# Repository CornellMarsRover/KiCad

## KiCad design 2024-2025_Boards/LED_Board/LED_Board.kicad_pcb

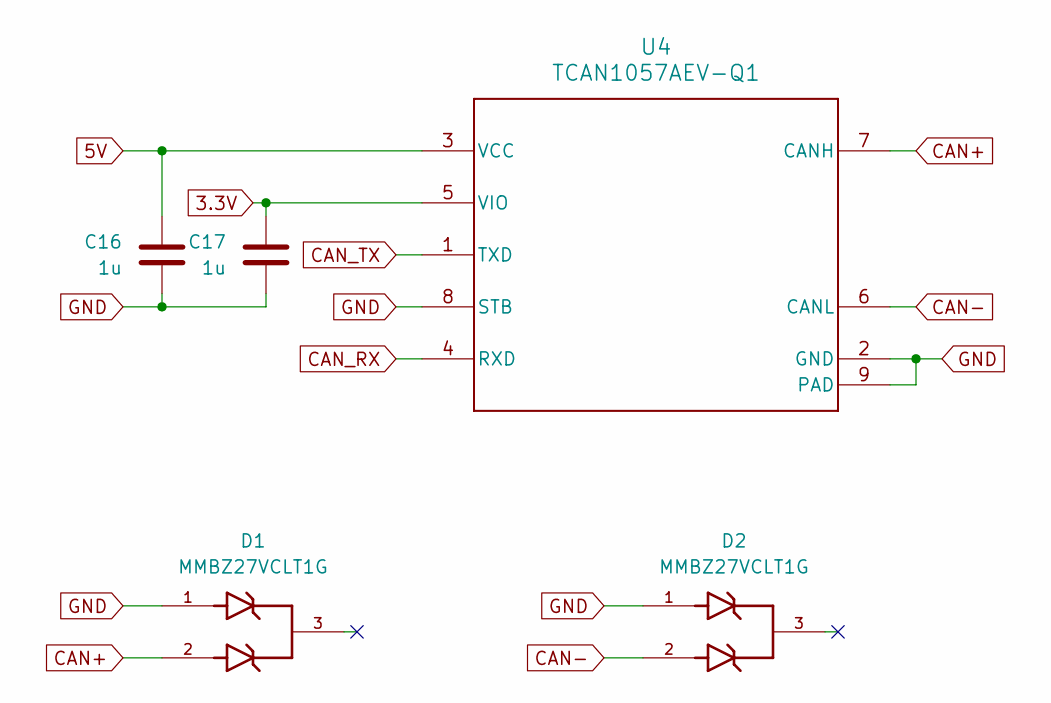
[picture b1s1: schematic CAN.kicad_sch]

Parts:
C16, C17: 1u; C_0402_1005Metric
D1, D2: MMBZ27VCLT1G; SOT95P237X111-3N; PARTREV 17
U4: TCAN1057AEV-Q1; SOIC-8_3.9x4.9mm_P1.27mm; MPN TCAN1057AEVDRQ1

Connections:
3.3V: C17.1, U4.5 (VIO); also elsewhere on the board
5V: C16.1, U4.3 (VCC); also elsewhere on the board
CAN+: D1.2, U4.7 (CANH); also elsewhere on the board
CAN-: D2.2, U4.6 (CANL); also elsewhere on the board
CAN_RX: U4.4 (RXD); also elsewhere on the board
CAN_TX: U4.1 (TXD); also elsewhere on the board
GND: C16.2, C17.2, D1.1, D2.1, U4.2 (GND), U4.8 (STB), U4.9 (PAD); also elsewhere on the board

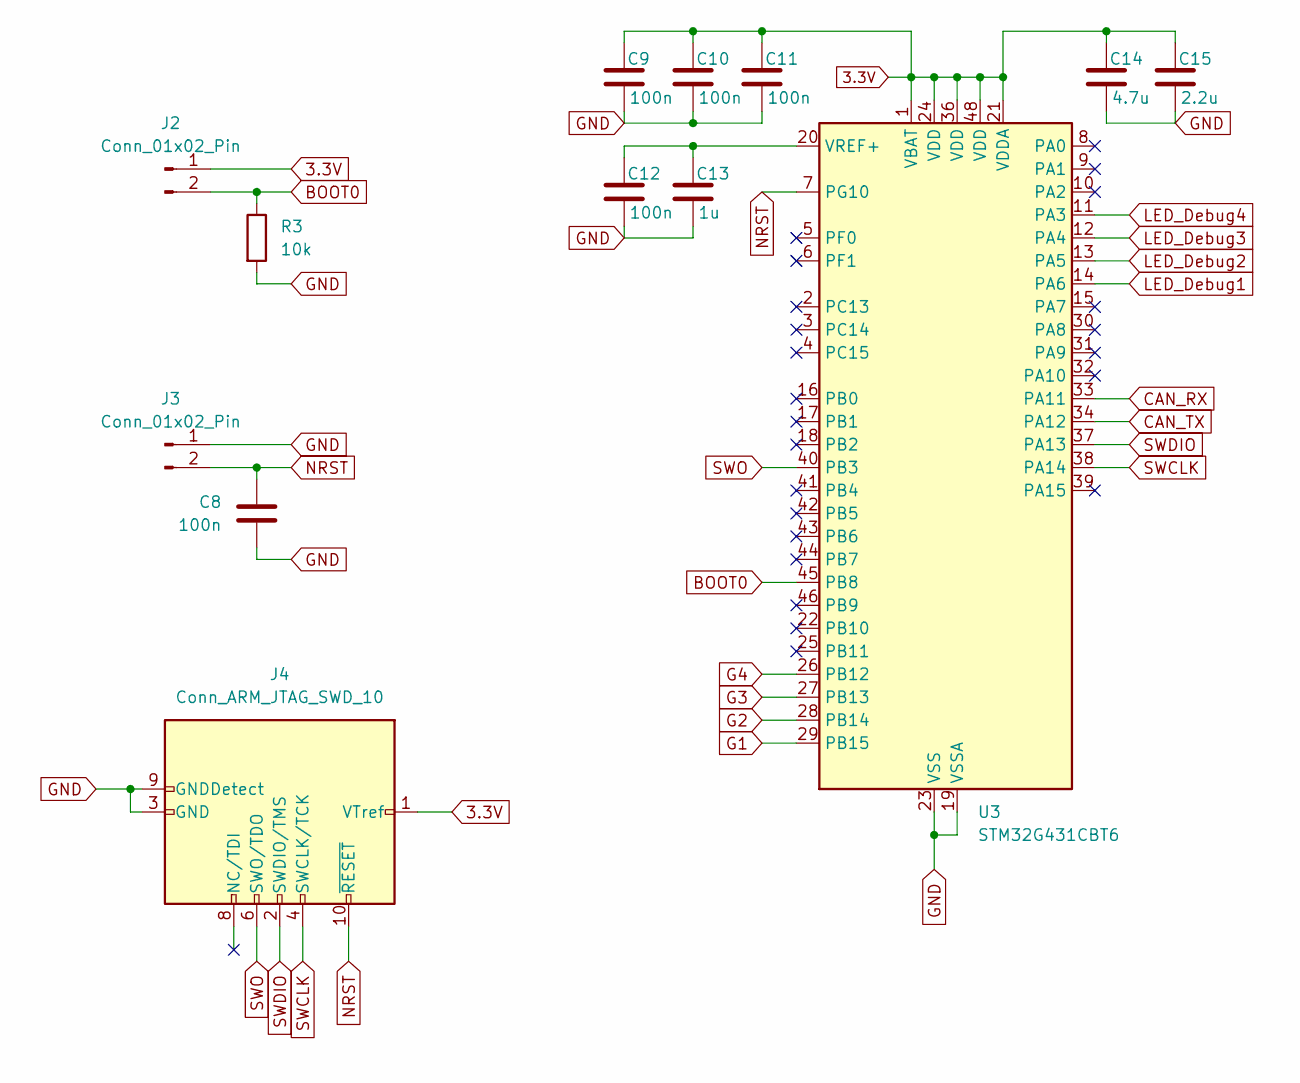
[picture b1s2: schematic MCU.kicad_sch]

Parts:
C8, C9, C10, C11, C12: 100n; C_0402_1005Metric
C13: 1u; C_0402_1005Metric
C14: 4.7u; C_0603_1608Metric
C15: 2.2u; C_0603_1608Metric
J2, J3: Conn_01x02_Pin; PinHeader_1x02_P2.54mm_Horizontal
J4: Conn_ARM_JTAG_SWD_10; PinHeader_2x05_P1.27mm_Vertical
R3: 10k; R_0402_1005Metric
U3: STM32G431CBT6; LQFP-48_7x7mm_P0.5mm

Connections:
3.3V: C9.1, C10.1, C11.1, C14.1, C15.1, J2.1, J4.1 (VTref), U3.1 (VBAT), U3.21 (VDDA), U3.24 (VDD), U3.36 (VDD), U3.48 (VDD); also elsewhere on the board
BOOT0: J2.2, R3.1, U3.45 (PB8)
CAN_RX: U3.33 (PA11); also elsewhere on the board
CAN_TX: U3.34 (PA12); also elsewhere on the board
G1: U3.29 (PB15); also elsewhere on the board
G2: U3.28 (PB14); also elsewhere on the board
G3: U3.27 (PB13); also elsewhere on the board
G4: U3.26 (PB12); also elsewhere on the board
GND: C8.2, C9.2, C10.2, C11.2, C12.2, C13.2, C14.2, C15.2, J3.1, J4.3 (GND), J4.5 (GND), J4.9 (GNDDetect), R3.2, U3.19 (VSSA), U3.23 (VSS), U3.35 (VSS), U3.47 (VSS); also elsewhere on the board
LED_Debug1: U3.14 (PA6); also elsewhere on the board
LED_Debug2: U3.13 (PA5); also elsewhere on the board
LED_Debug3: U3.12 (PA4); also elsewhere on the board
LED_Debug4: U3.11 (PA3); also elsewhere on the board
NRST: C8.1, J3.2, J4.10 (~RESET), U3.7 (PG10); also elsewhere on the board
unnamed: C12.1, C13.1, U3.20 (VREF+)
SWCLK: J4.4 (SWCLK/TCK), U3.38 (PA14)
SWDIO: J4.2 (SWDIO/TMS), U3.37 (PA13)
SWO: J4.6 (SWO/TDO), U3.40 (PB3)

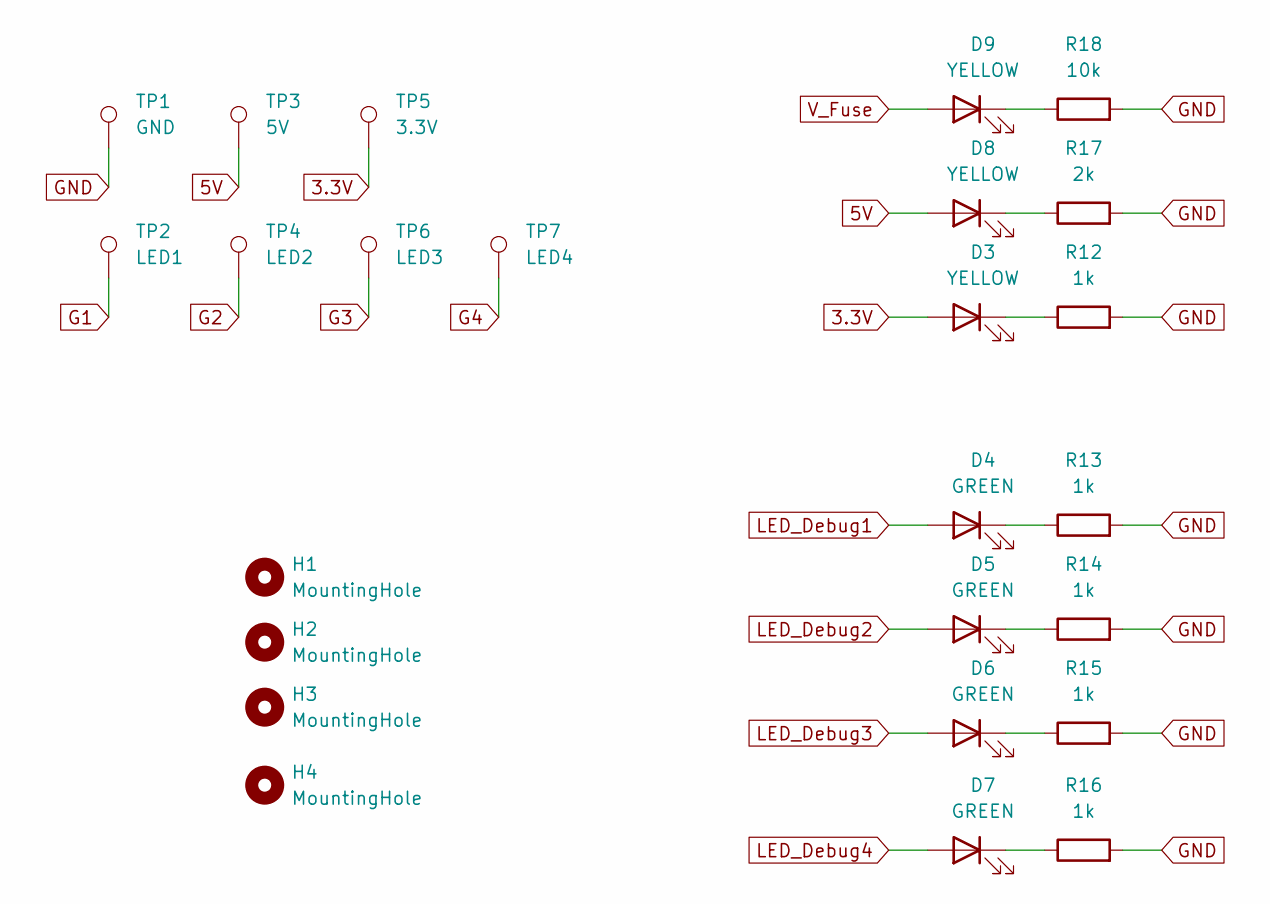
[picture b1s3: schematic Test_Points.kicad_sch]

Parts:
D3, D8, D9: YELLOW; LED_0603_1608Metric
D4, D5, D6, D7: GREEN; LED_0603_1608Metric
H1, H2, H3, H4: MountingHole; MountingHole_2.7mm_M2.5
R12, R13, R14, R15, R16: 1k; R_0402_1005Metric
R17: 2k; R_0402_1005Metric
R18: 10k; R_0402_1005Metric
TP1: GND; TestPoint_Pad_D1.0mm
TP2: LED1; TestPoint_Pad_D1.0mm
TP3: 5V; TestPoint_Pad_D1.0mm
TP4: LED2; TestPoint_Pad_D1.0mm
TP5: 3.3V; TestPoint_Pad_D1.0mm
TP6: LED3; TestPoint_Pad_D1.0mm
TP7: LED4; TestPoint_Pad_D1.0mm

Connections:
3.3V: D3.2 (A), TP5.1; also elsewhere on the board
5V: D8.2 (A), TP3.1; also elsewhere on the board
G1: TP2.1; also elsewhere on the board
G2: TP4.1; also elsewhere on the board
G3: TP6.1; also elsewhere on the board
G4: TP7.1; also elsewhere on the board
GND: R12.2, R13.2, R14.2, R15.2, R16.2, R17.2, R18.2, TP1.1; also elsewhere on the board
LED_Debug1: D4.2 (A); also elsewhere on the board
LED_Debug2: D5.2 (A); also elsewhere on the board
LED_Debug3: D6.2 (A); also elsewhere on the board
LED_Debug4: D7.2 (A); also elsewhere on the board
unnamed: D3.1 (K), R12.1
unnamed: D4.1 (K), R13.1
unnamed: D5.1 (K), R14.1
unnamed: D6.1 (K), R15.1
unnamed: D7.1 (K), R16.1
unnamed: D8.1 (K), R17.1
unnamed: D9.1 (K), R18.1
V_Fuse: D9.2 (A); also elsewhere on the board

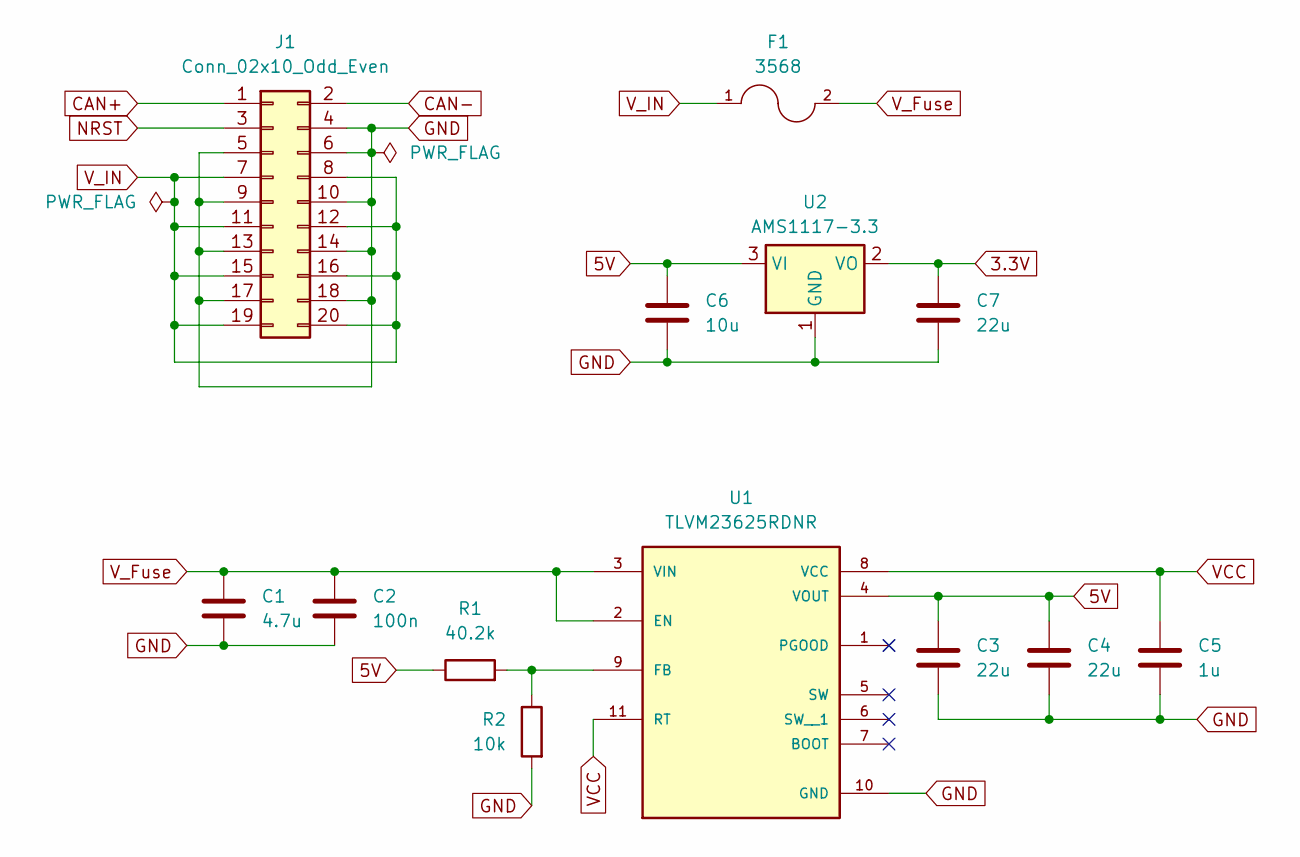
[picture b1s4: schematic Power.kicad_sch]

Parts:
C1: 4.7u; C_0805_2012Metric
C2: 100n; C_0402_1005Metric
C3, C4, C7: 22u; C_0805_2012Metric
C5: 1u; C_0402_1005Metric
C6: 10u; C_0805_2012Metric
F1: 3568; FUSE_3568; PARTREV C
J1: Conn_02x10_Odd_Even; CONN20_D10-RA-BK_SUL
R1: 40.2k; R_0603_1608Metric
R2: 10k; R_0603_1608Metric
U1: TLVM23625RDNR; RDN0011A-MFG; PARTREV B
U2: AMS1117-3.3; SOT-223-3_TabPin2

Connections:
3.3V: C7.1, U2.2 (VO); also elsewhere on the board
5V: C3.1, C4.1, C6.1, R1.1, U1.4 (VOUT), U2.3 (VI); also elsewhere on the board
CAN+: J1.1; also elsewhere on the board
CAN-: J1.2; also elsewhere on the board
GND: C1.2, C2.2, C3.2, C4.2, C5.2, C6.2, C7.2, J1.4, J1.5, J1.6, J1.9, J1.10, J1.13, J1.14, J1.17, J1.18, R2.2, U1.10 (GND), U2.1 (GND); also elsewhere on the board
NRST: J1.3; also elsewhere on the board
unnamed: R1.2, R2.1, U1.9 (FB)
VCC: C5.1, U1.8 (VCC), U1.11 (RT)
V_Fuse: C1.1, C2.1, F1.2, F1.4, U1.2 (EN), U1.3 (VIN); also elsewhere on the board
V_IN: F1.1, F1.3, J1.7, J1.8, J1.11, J1.12, J1.15, J1.16, J1.19, J1.20

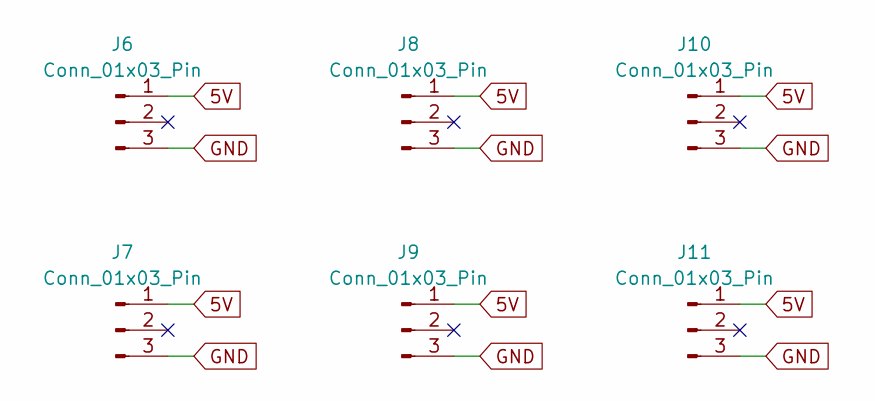
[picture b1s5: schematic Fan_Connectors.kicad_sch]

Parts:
J6, J7, J8, J9, J10, J11: Conn_01x03_Pin; CONN_A-7395-03B_MOL

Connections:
5V: J6.1, J7.1, J8.1, J9.1, J10.1, J11.1; also elsewhere on the board
GND: J6.3, J7.3, J8.3, J9.3, J10.3, J11.3; also elsewhere on the board

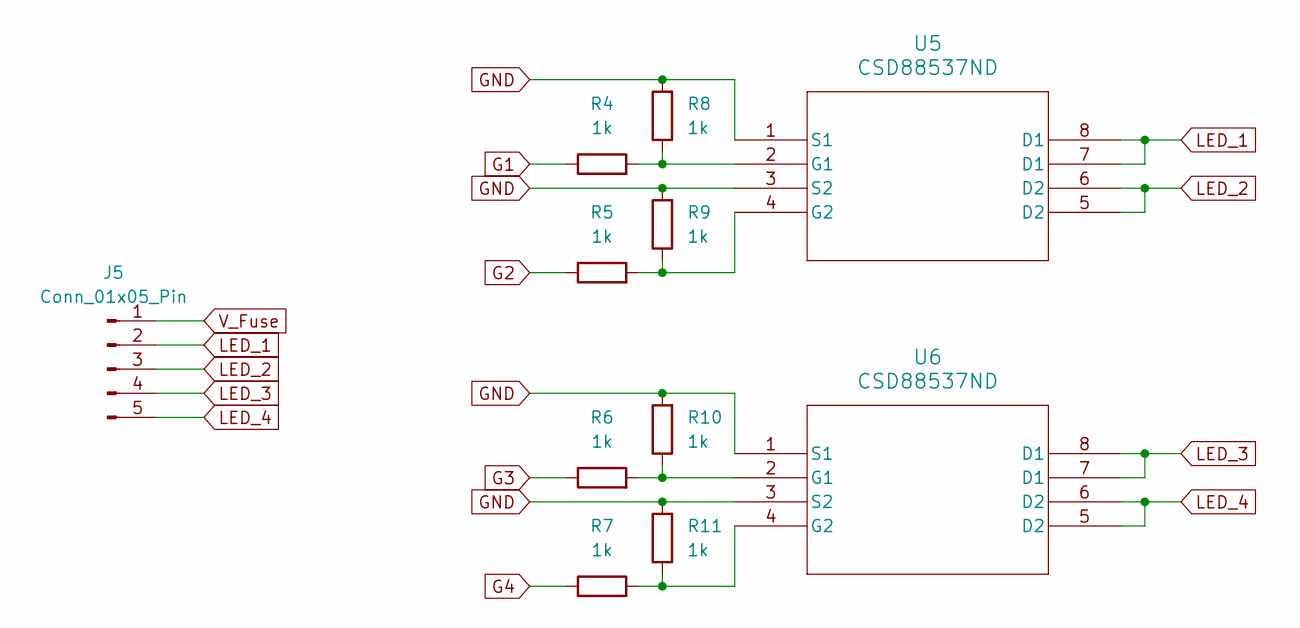
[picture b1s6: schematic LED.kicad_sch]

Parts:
J5: Conn_01x05_Pin; JST_EH_S5B-EH_1x05_P2.50mm_Horizontal
R4, R5, R6, R7, R8, R9, R10, R11: 1k; R_0402_1005Metric
U5, U6: CSD88537ND; CSD88537ND8-M

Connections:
G1: R4.1; also elsewhere on the board
G2: R5.1; also elsewhere on the board
G3: R6.1; also elsewhere on the board
G4: R7.1; also elsewhere on the board
GND: R8.2, R9.2, R10.2, R11.2, U5.1 (S1), U5.3 (S2), U6.1 (S1), U6.3 (S2); also elsewhere on the board
LED_1: J5.2, U5.7 (D1), U5.8 (D1)
LED_2: J5.3, U5.5 (D2), U5.6 (D2)
LED_3: J5.4, U6.7 (D1), U6.8 (D1)
LED_4: J5.5, U6.5 (D2), U6.6 (D2)
unnamed: R4.2, R8.1, U5.2 (G1)
unnamed: R5.2, R9.1, U5.4 (G2)
unnamed: R6.2, R10.1, U6.2 (G1)
unnamed: R7.2, R11.1, U6.4 (G2)
V_Fuse: J5.1; also elsewhere on the board

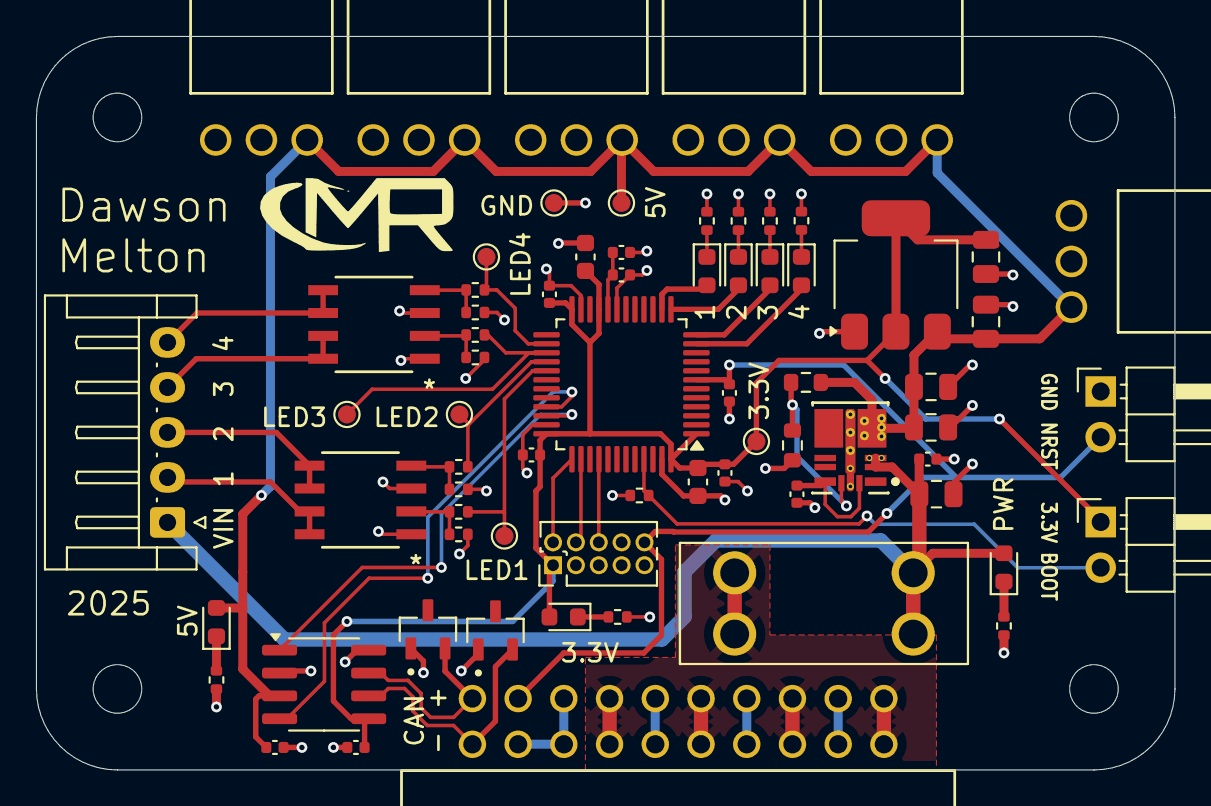
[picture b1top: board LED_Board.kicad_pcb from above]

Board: 2 copper layers, 63.2 x 40.7 mm, 73 parts (0 on the bottom side), 40 nets.

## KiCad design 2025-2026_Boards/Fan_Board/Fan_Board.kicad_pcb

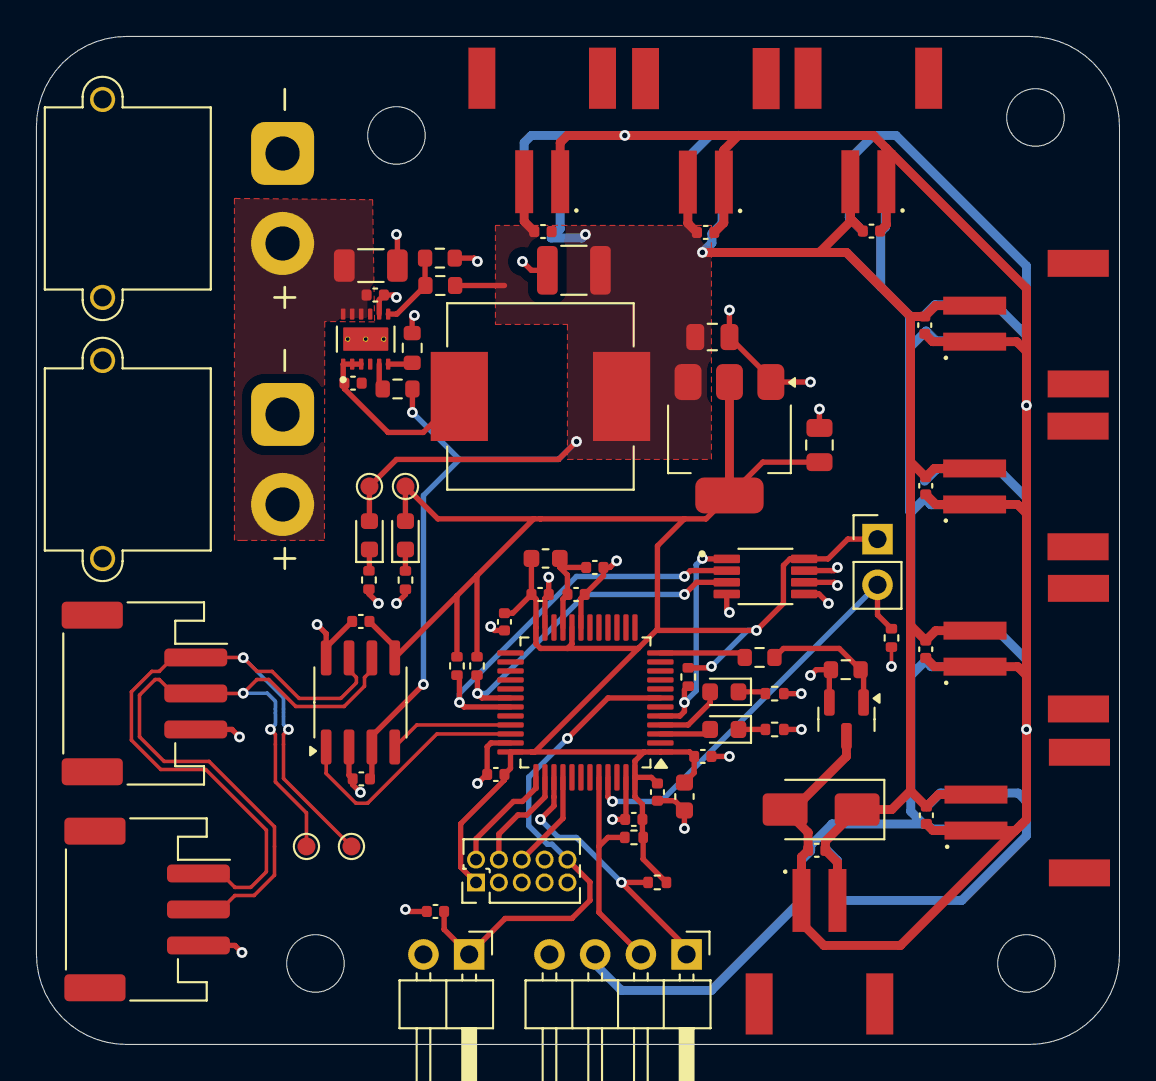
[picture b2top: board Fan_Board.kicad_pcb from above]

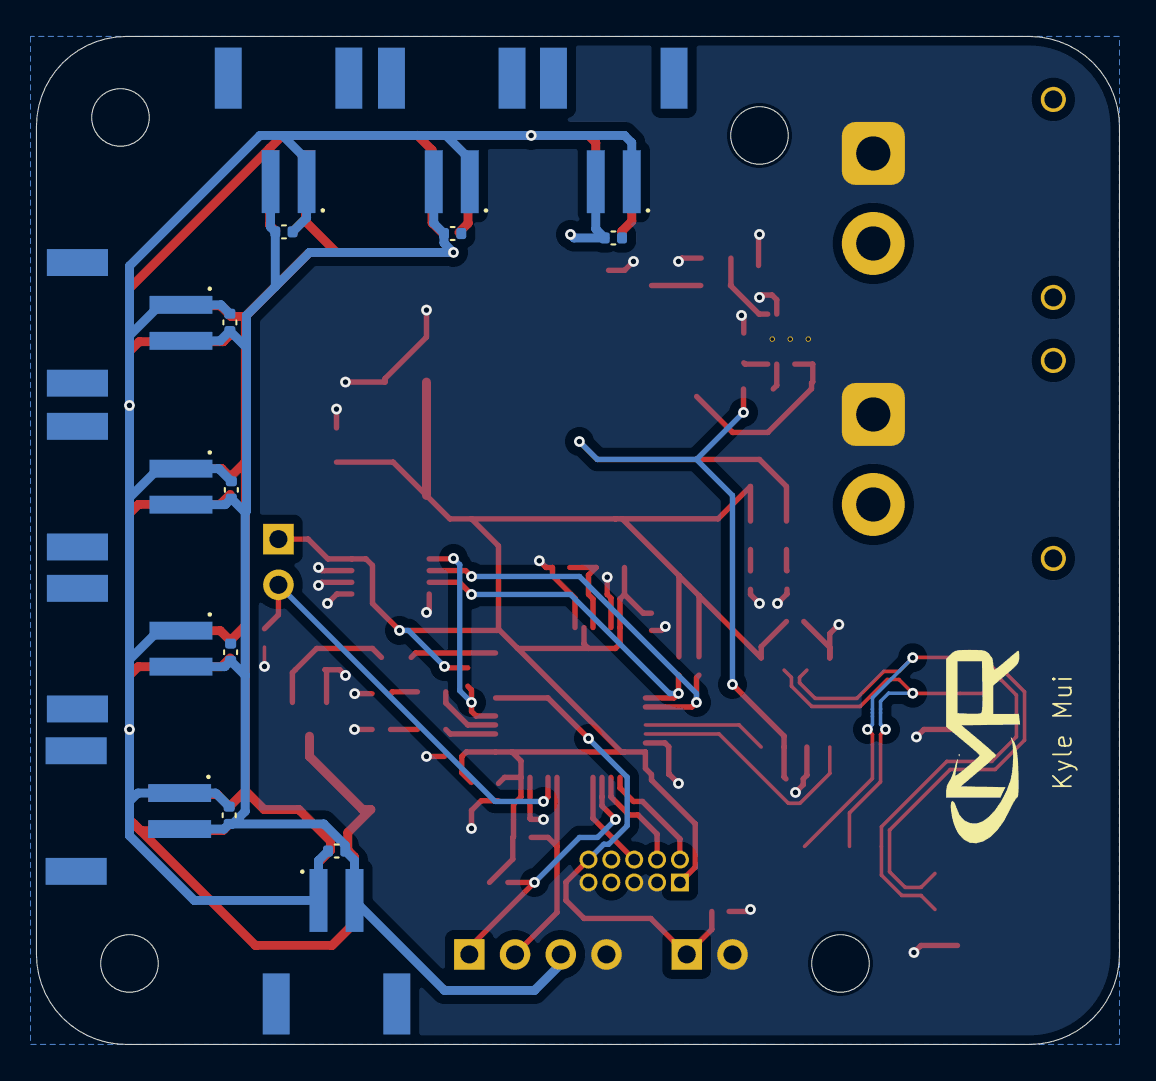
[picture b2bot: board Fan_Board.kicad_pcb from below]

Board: 2 copper layers, 60.2 x 56.0 mm, 95 parts (16 on the bottom side), 33 nets.

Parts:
C1, C2: 22u; C_0805_2012Metric
C3, C6, C7, C18, C19, C20, C21, C22, C23, C24, C25, C26, C29, C30, C31, C32, C33, C34: 100nF; C_0402_1005Metric
C4: 47uF; C_1210_3225Metric
C5: 4.7uF; C_1206_3216Metric
C8: 10u; C_0603_1608Metric
C9, C10, C11, C12, C13, C17, C27, C28: 100n; C_0402_1005Metric
C14: 10n; C_0402_1005Metric
C15, C16: 1u; C_0402_1005Metric
D1, D2: RED; LED_0603_1608Metric
D3: SS34; D_SMA
D17, D18: BLUE; LED_0603_1608Metric
FB1: 120R; L_0603_1608Metric
H1, H2, H3, H4: MountingHole; MountingHole_3.2mm_M3
J1: Conn_01x02_Pin; PinHeader_1x02_P2.54mm_Horizontal
J2: Conn_ARM_JTAG_SWD_10; PinHeader_2x05_P1.27mm_Vertical
J3, J4, J5, J6, J7, J8, J9, J10, J11, J12, J13, J14, J15, J16, J17, J18: Conn_01x02_Pin; JST_S2B-PH-SM4-TB
J19, J20: Conn_01x03_Socket; JST_PH_S3B-PH-SM4-TB_1x03-1MP_P2.00mm_Horizontal
J21: Conn_01x02_Pin; PinHeader_1x02_P2.54mm_Vertical
J22, J23: Conn_01x02_Socket; AMASS_XT30PW-M_1x02_P2.50mm_Horizontal
J24: Conn_01x04_Pin; PinHeader_1x04_P2.54mm_Horizontal
L1: 5.6uH; L_Vishay_IHLP-4040
Q1: AO3400A; SOT-23
R1, R14, R29, R30: 2.2k; R_0402_1005Metric
R2, R4, R9: 100k; R_0603_1608Metric
R3: 30.9k; R_0603_1608Metric
R5: 220; R_0603_1608Metric
R6: 10k; R_0402_1005Metric
R7, R8, R10, R11, R12: 5k; R_0402_1005Metric
R13: 19.1k; R_0603_1608Metric
TP1, TP2, TP3, TP4: TestPoint; TestPoint_Pad_D1.0mm
U1: AMS1117-3.3; SOT-223-3_TabPin2
U2: LMR51450SDRRR; CONV_LMR51450SDRRR
U3: STM32G431CBT6; LQFP-48_7x7mm_P0.5mm
U4: TMP275AIDGKR; SOP65P490X110-8N
U6: TCAN1057AEV-Q1; SOIC-8_3.9x4.9mm_P1.27mm

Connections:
+3.3V: C2.1, C8.1, C9.1, C10.1, C11.1, C12.1, C13.1, C16.1, C28.1, D1.2 (A), FB1.2, J2.1 (VTref), J21.1, R7.2, R8.2, R10.2, R11.1, R12.1, TP1.1, U1.2 (VO), U3.1 (VBAT), U3.20 (VREF+), U3.24 (VDD), U3.36 (VDD), U3.48 (VDD), U4.8 (V+), U6.5 (VIO)
+3.3VA: C14.1, C15.1, FB1.1, U3.21 (VDDA)
+5V: C1.1, C4.1, C7.1, C18.1, C19.1, C20.1, C21.1, C22.1, C23.1, C24.1, C25.1, C26.1, C27.1, C29.1, C30.1, C31.1, C32.1, C33.1, C34.1, D2.2 (A), D3.1 (K), J3.2, J4.2, J5.2, J6.2, J7.2, J8.2, J9.2, J10.2, J11.2, J12.2, J13.2, J14.2, J15.2, J16.2, J17.2, J18.2, J24.3, L1.2, R2.2, R9.2, TP2.1, U1.3 (VI), U6.3 (VCC)
+BATT: C5.1, C6.1, J22.2, J23.2, U2.9 (EN), U2.10 (VIN), U2.11 (VIN__1), U2.12 (VIN__2)
/MCU/BOOT0: J21.2, R6.1, U3.45 (PB8)
/MCU/LED1: D17.2 (A), U3.3 (PC14)
/MCU/LED2: D18.2 (A), U3.4 (PC15)
/MCU/SWCLK: J2.4 (SWCLK/TCK), U3.38 (PA14)
/MCU/SWDIO: J2.2 (SWDIO/TMS), U3.37 (PA13)
Alert: R12.2, U3.30 (PA8), U4.3 (ALERT)
CAN+: J19.1, J20.1, TP3.1, U6.7 (CANH)
CAN-: J19.2, J20.2, TP4.1, U6.6 (CANL)
FDCAN_RX: U3.33 (PA11), U6.4 (RXD)
FDCAN_TX: U3.34 (PA12), U6.1 (TXD)
Fan_On: R5.1, U3.12 (PA4)
GND: C1.2, C2.2, C4.2, C5.2, C6.2, C8.2, C9.2, C10.2, C11.2, C12.2, C13.2, C14.2, C15.2, C16.2, C17.2, C27.2, C28.2, J1.2, J2.3 (GND), J2.5 (GND), J2.9 (GNDDetect), J19.3, J20.3, J22.1, J23.1, J24.4, Q1.2 (S), R1.2, R3.1, R4.2, R6.2, R13.1, R14.2, R29.1, R30.1, U1.1 (GND), U2.8 (AGND), U2.13 (PGND), U3.19 (VSSA), U3.23 (VSS), U3.35 (VSS), U3.47 (VSS), U4.4 (GND), U4.5 (A2), U4.6 (A1), U4.7 (A0), U6.2 (GND), U6.8 (STB)
NREST: C17.1, J1.1, J2.10 (~RESET), U3.7 (PG10)
unnamed: D1.1 (K), R1.1
unnamed: D2.1 (K), R14.1
unnamed: C7.2, C18.2, C19.2, C20.2, C21.2, C22.2, C23.2, C24.2, C25.2, C26.2, C29.2, C30.2, C31.2, C32.2, C33.2, C34.2, D3.2 (A), J3.1, J4.1, J5.1, J6.1, J7.1, J8.1, J9.1, J10.1, J11.1, J12.1, J13.1, J14.1, J15.1, J16.1, J17.1, J18.1, Q1.3 (D)
unnamed: D17.1 (K), R29.2
unnamed: D18.1 (K), R30.2
unnamed: Q1.1 (G), R4.1, R5.2
unnamed: C3.1, U2.4 (BOOT)
unnamed: R9.1, R13.2, U2.7 (FB)
unnamed: R2.1, U2.5 (PG)
unnamed: R3.2, U2.6 (RT)
unnamed: C3.2, L1.1, U2.1 (SW), U2.2 (SW__1), U2.3 (SW__2)
SCL1: J24.1, R8.1, U3.39 (PA15)
SCL2: R11.2, U3.31 (PA9), U4.2 (SCL)
SDA1: J24.2, R7.1, U3.44 (PB7)
SDA2: R10.1, U3.5 (PF0), U4.1 (SDA)
SWO: J2.6 (SWO/TDO), U3.40 (PB3)

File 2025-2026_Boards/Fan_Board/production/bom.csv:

Designator,Footprint,Quantity,Value,LCSC Part #
"C1, C2",0805,2,22u,
"C10, C11, C12, C13, C17, C27, C28, C9",0402,8,100n,
C14,0402,1,10n,
"C15, C16",0402,2,1u,
"C18, C19, C20, C21, C22, C23, C24, C25, C26, C29, C3, C30, C31, C32, C33, C34, C6, C7",0402,18,100nF,
C4,1210,1,47uF,
C5,1206,1,4.7uF,
C8,0603,1,10u,
"D1, D2",0603,2,RED,
"D17, D18",0603,2,BLUE,
D3,D_SMA,1,SS34,
FB1,0603,1,120R,
J1,PinHeader_1x02_P2.54mm_Horizontal,1,Conn_01x02_Pin,
"J10, J11, J12, J13, J14, J15, J16, J17, J18, J3, J4, J5, J6, J7, J8, J9",JST_S2B-PH-SM4-TB,16,Conn_01x02_Pin,
"J19, J20",JST_PH_S3B-PH-SM4-TB_1x03-1MP_P2.00mm_Horizontal,2,Conn_01x03_Socket,
J2,PinHeader_2x05_P1.27mm_Vertical,1,Conn_ARM_JTAG_SWD_10,
J21,PinHeader_1x02_P2.54mm_Vertical,1,Conn_01x02_Pin,
"J22, J23",AMASS_XT30PW-M_1x02_P2.50mm_Horizontal,2,Conn_01x02_Socket,
J24,PinHeader_1x04_P2.54mm_Horizontal,1,Conn_01x04_Pin,
L1,L_Vishay_IHLP-4040,1,5.6uH,
Q1,SOT-23,1,AO3400A,
"R1, R14, R29, R30",0402,4,2.2k,
"R10, R11, R12, R7, R8",0402,5,5k,
R13,0603,1,19.1k,
"R2, R4, R9",0603,3,100k,
R3,0603,1,30.9k,
R5,0603,1,220,
R6,0402,1,10k,
U1,SOT-223-3_TabPin2,1,AMS1117-3.3,
U2,CONV_LMR51450SDRRR,1,LMR51450SDRRR,
U3,LQFP-48_7x7mm_P0.5mm,1,STM32G431CBT6,
U4,SOP65P490X110-8N,1,TMP275AIDGKR,
U6,SOIC-8_3.9x4.9mm_P1.27mm,1,TCAN1057AEV-Q1,TCAN1057AEVDRQ1

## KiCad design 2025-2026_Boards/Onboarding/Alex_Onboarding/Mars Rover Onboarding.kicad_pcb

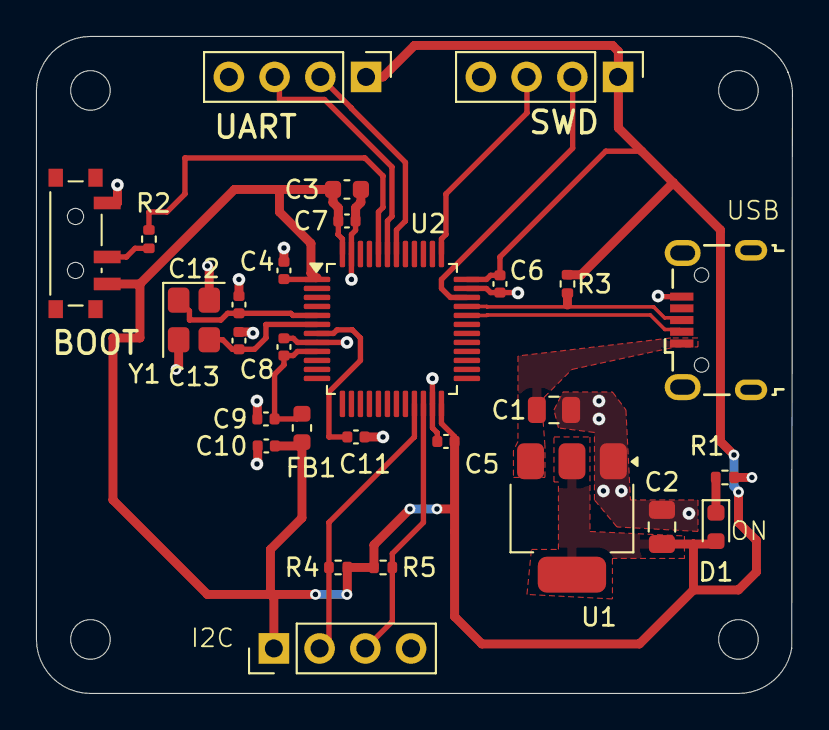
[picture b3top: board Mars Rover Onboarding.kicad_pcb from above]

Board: 2 copper layers, 42.0 x 36.5 mm, 32 parts (0 on the bottom side), 17 nets.

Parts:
C1, C2: 22u; C_0805_2012Metric
C3: 10u; C_0603_1608Metric
C4, C5, C6, C7, C11: 100n; C_0402_1005Metric
C8: 10n; C_0402_1005Metric
C9, C10: 1u; C_0402_1005Metric
C12, C13: 10p; C_0402_1005Metric
D1: RED; LED_0603_1608Metric
FB1: 120R; L_0603_1608Metric
H1, H2, H3, H4: MountingHole; MountingHole_2.2mm_M2
J1: USB_B_Micro; USB_Micro-B_Wuerth_629105150521
J2, J3, J4: Conn_01x04_Pin; PinHeader_1x04_P2.54mm_Vertical
R1, R3, R4, R5: 1k5; R_0402_1005Metric
R2: 10k; R_0402_1005Metric
SW1: SW_SPDT; SW_SPDT_PCM12
U1: AMS1117-3.3; SOT-223-3_TabPin2
U2: STM32F103C8T6; LQFP-48_7x7mm_P0.5mm
Y1: 16MHz; Crystal_SMD_3225-4Pin_3.2x2.5mm

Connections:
+3.3V: C2.1, C3.1, C4.1, C5.1, C6.1, C7.1, C10.1, D1.2 (A), FB1.2, J2.1, J3.1, J4.1, R3.1, R4.1, R5.1, SW1.3 (C), U1.2 (VO), U2.1 (VBAT), U2.24 (VDD), U2.36 (VDD), U2.48 (VDD)
+3.3VA: C8.1, C9.1, FB1.1, U2.9 (VDDA)
/HSE_IN: C12.1, U2.5 (PD0), Y1.1
/HSE_OUT: C13.1, U2.6 (PD1), Y1.3
/I2C2_SCL: J4.2, R4.2, U2.21 (PB10)
/I2C2_SDA: J4.3, R5.2, U2.22 (PB11)
/NRST: C11.1, U2.7 (NRST)
/SWCLK: J3.3, U2.37 (PA14)
/SWDIO: J3.2, U2.34 (PA13)
/SW_BOOT0: R2.1, R2.2, SW1.2 (B), U2.44 (BOOT0)
/USART1_RX: J2.3, U2.43 (PB7)
/USART1_TX: J2.2, U2.42 (PB6)
/USB_D+: J1.3 (D+), R3.2, U2.33 (PA12)
/USB_D-: J1.2 (D-), U2.32 (PA11)
GND: C1.2, C2.2, C3.2, C4.2, C5.2, C6.2, C7.2, C8.2, C9.2, C10.2, C11.2, C12.2, C13.2, J1.5 (GND), J2.4, J3.4, J4.4, R1.2, SW1.1 (A), U1.1 (GND), U2.8 (VSSA), U2.23 (VSS), U2.35 (VSS), U2.47 (VSS), Y1.2, Y1.4
unnamed: D1.1 (K), R1.1
VBUS: C1.1, J1.1 (VBUS), U1.3 (VI)
